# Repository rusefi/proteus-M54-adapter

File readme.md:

Proteus adapter for e46 non-M3 BMW

(E39 m54 should be the ms42/43 like the e46, E39 ~= E46)

https://github.com/rusefi/rusefi/wiki/BMW-e46

134 pin + Nissan board outline

https://raw.githubusercontent.com/wiki/rusefi/rusefi/OEM-Docs/Bmw/3_Series_e46/2002_bmw_325_ecu.png

https://docs.google.com/spreadsheets/d/16_VjNrk-DbMP_yDqGFelwavrGfiC9wFp73RgForjQzM

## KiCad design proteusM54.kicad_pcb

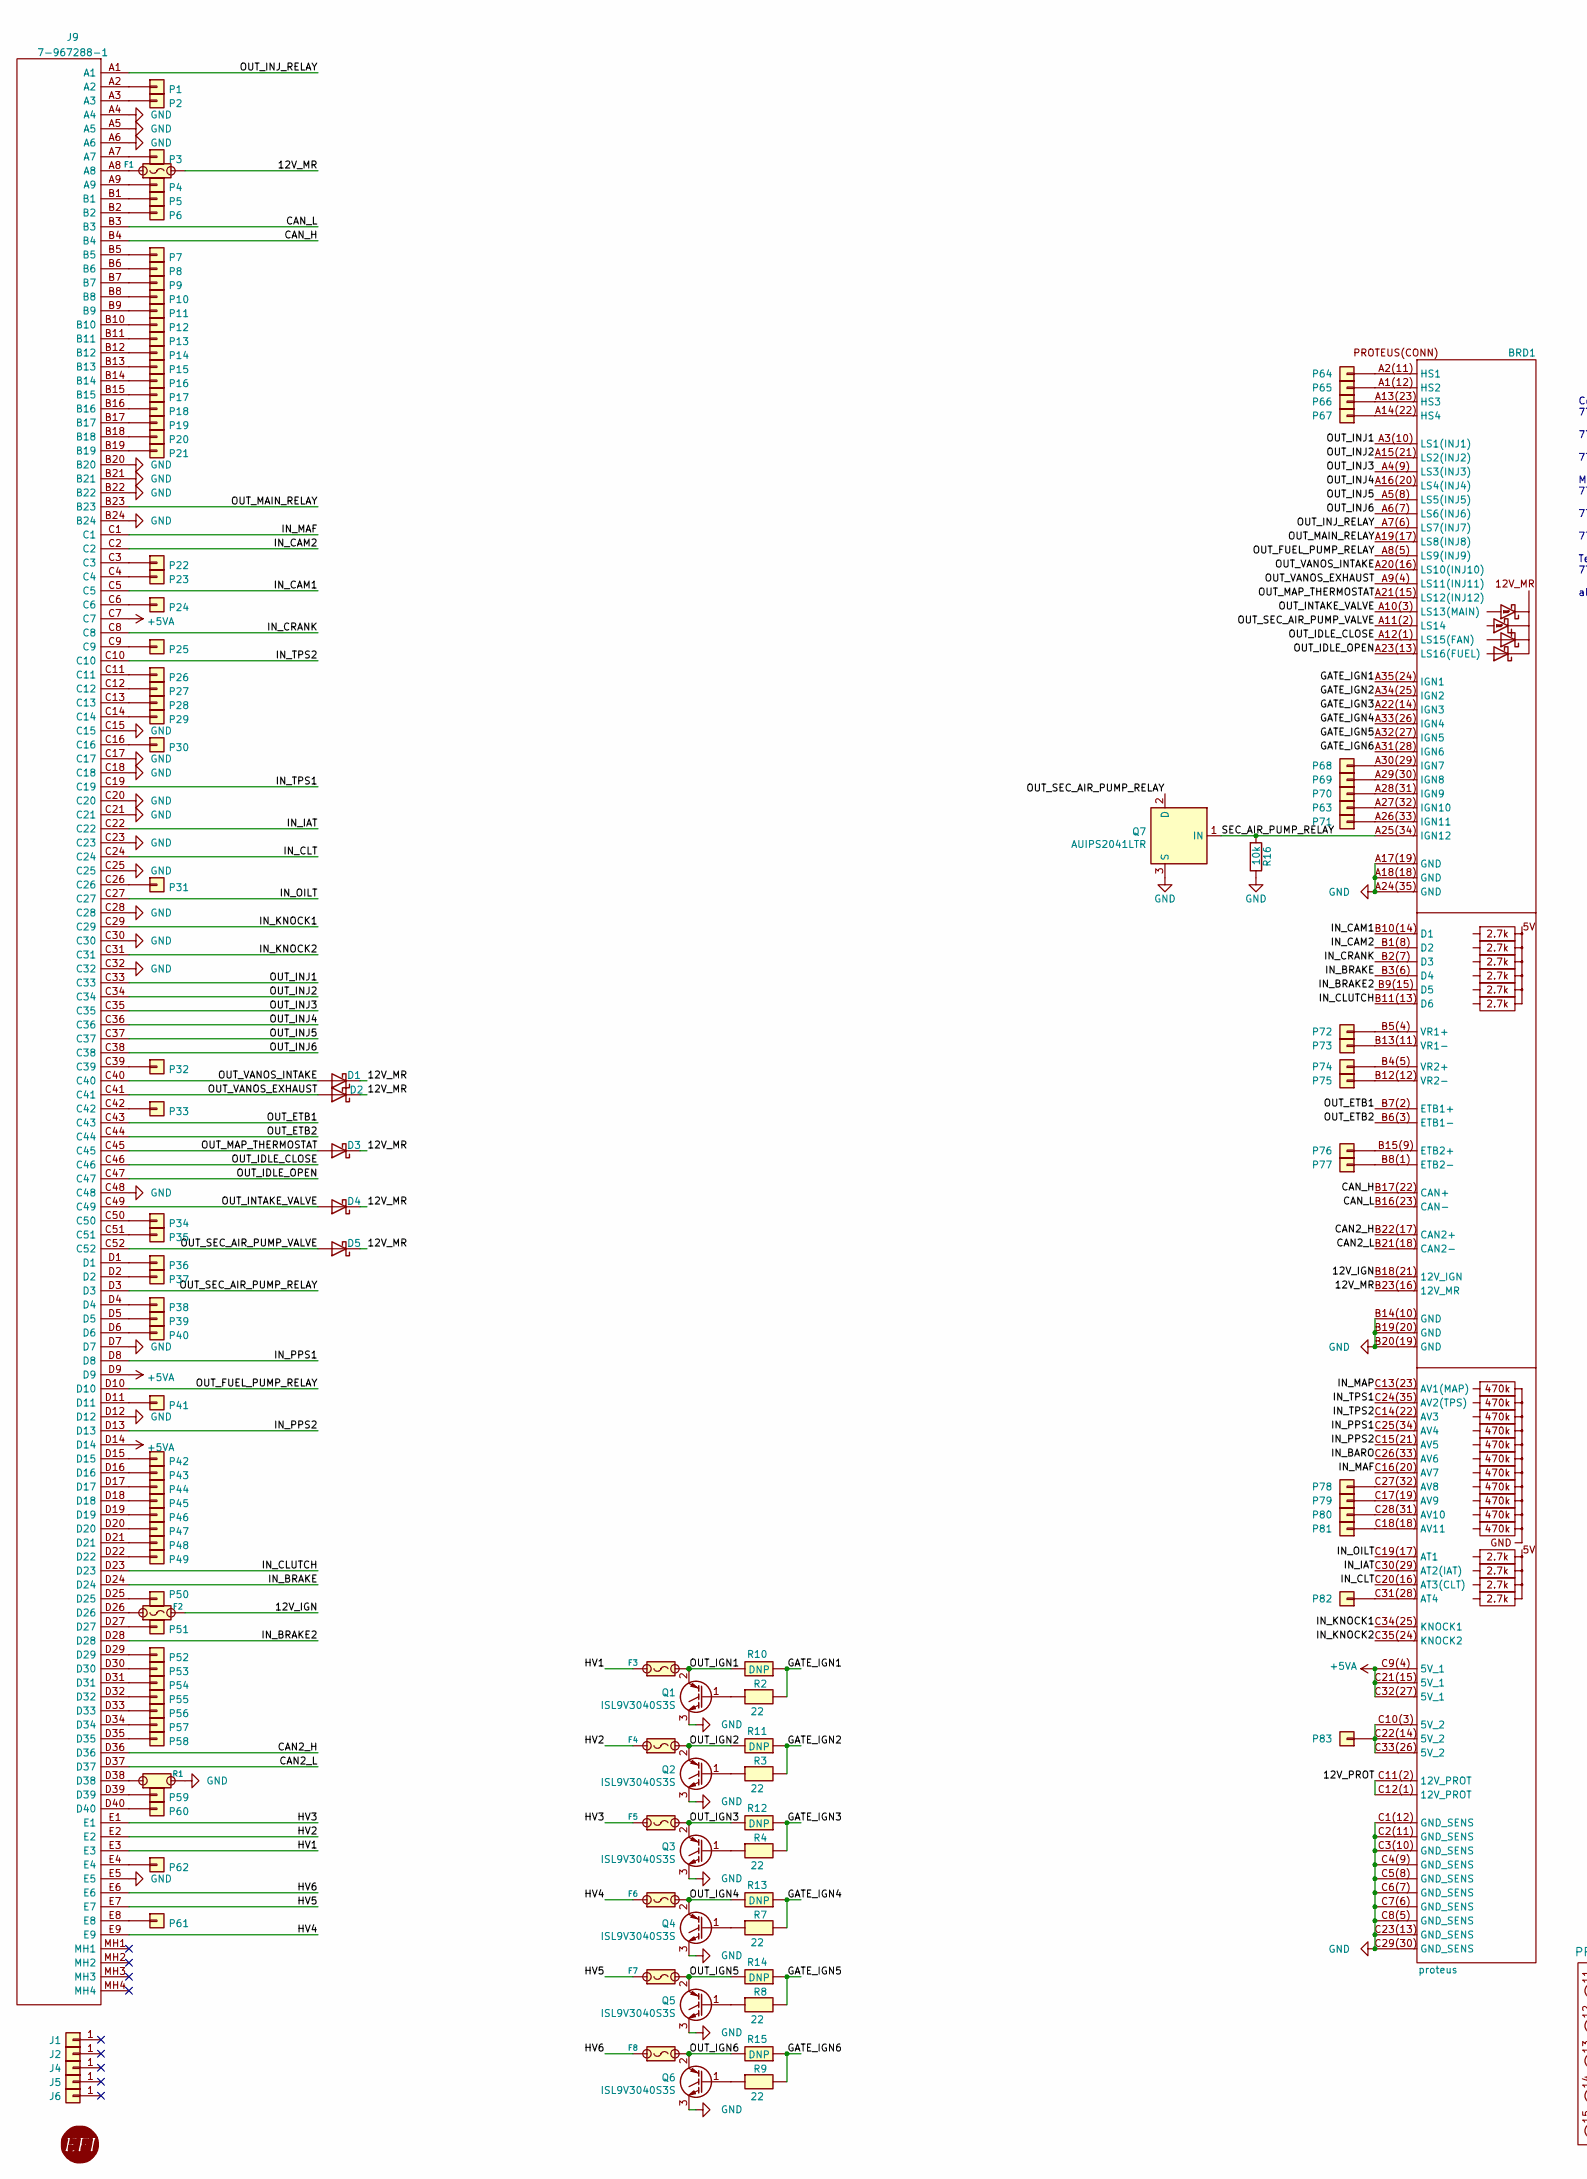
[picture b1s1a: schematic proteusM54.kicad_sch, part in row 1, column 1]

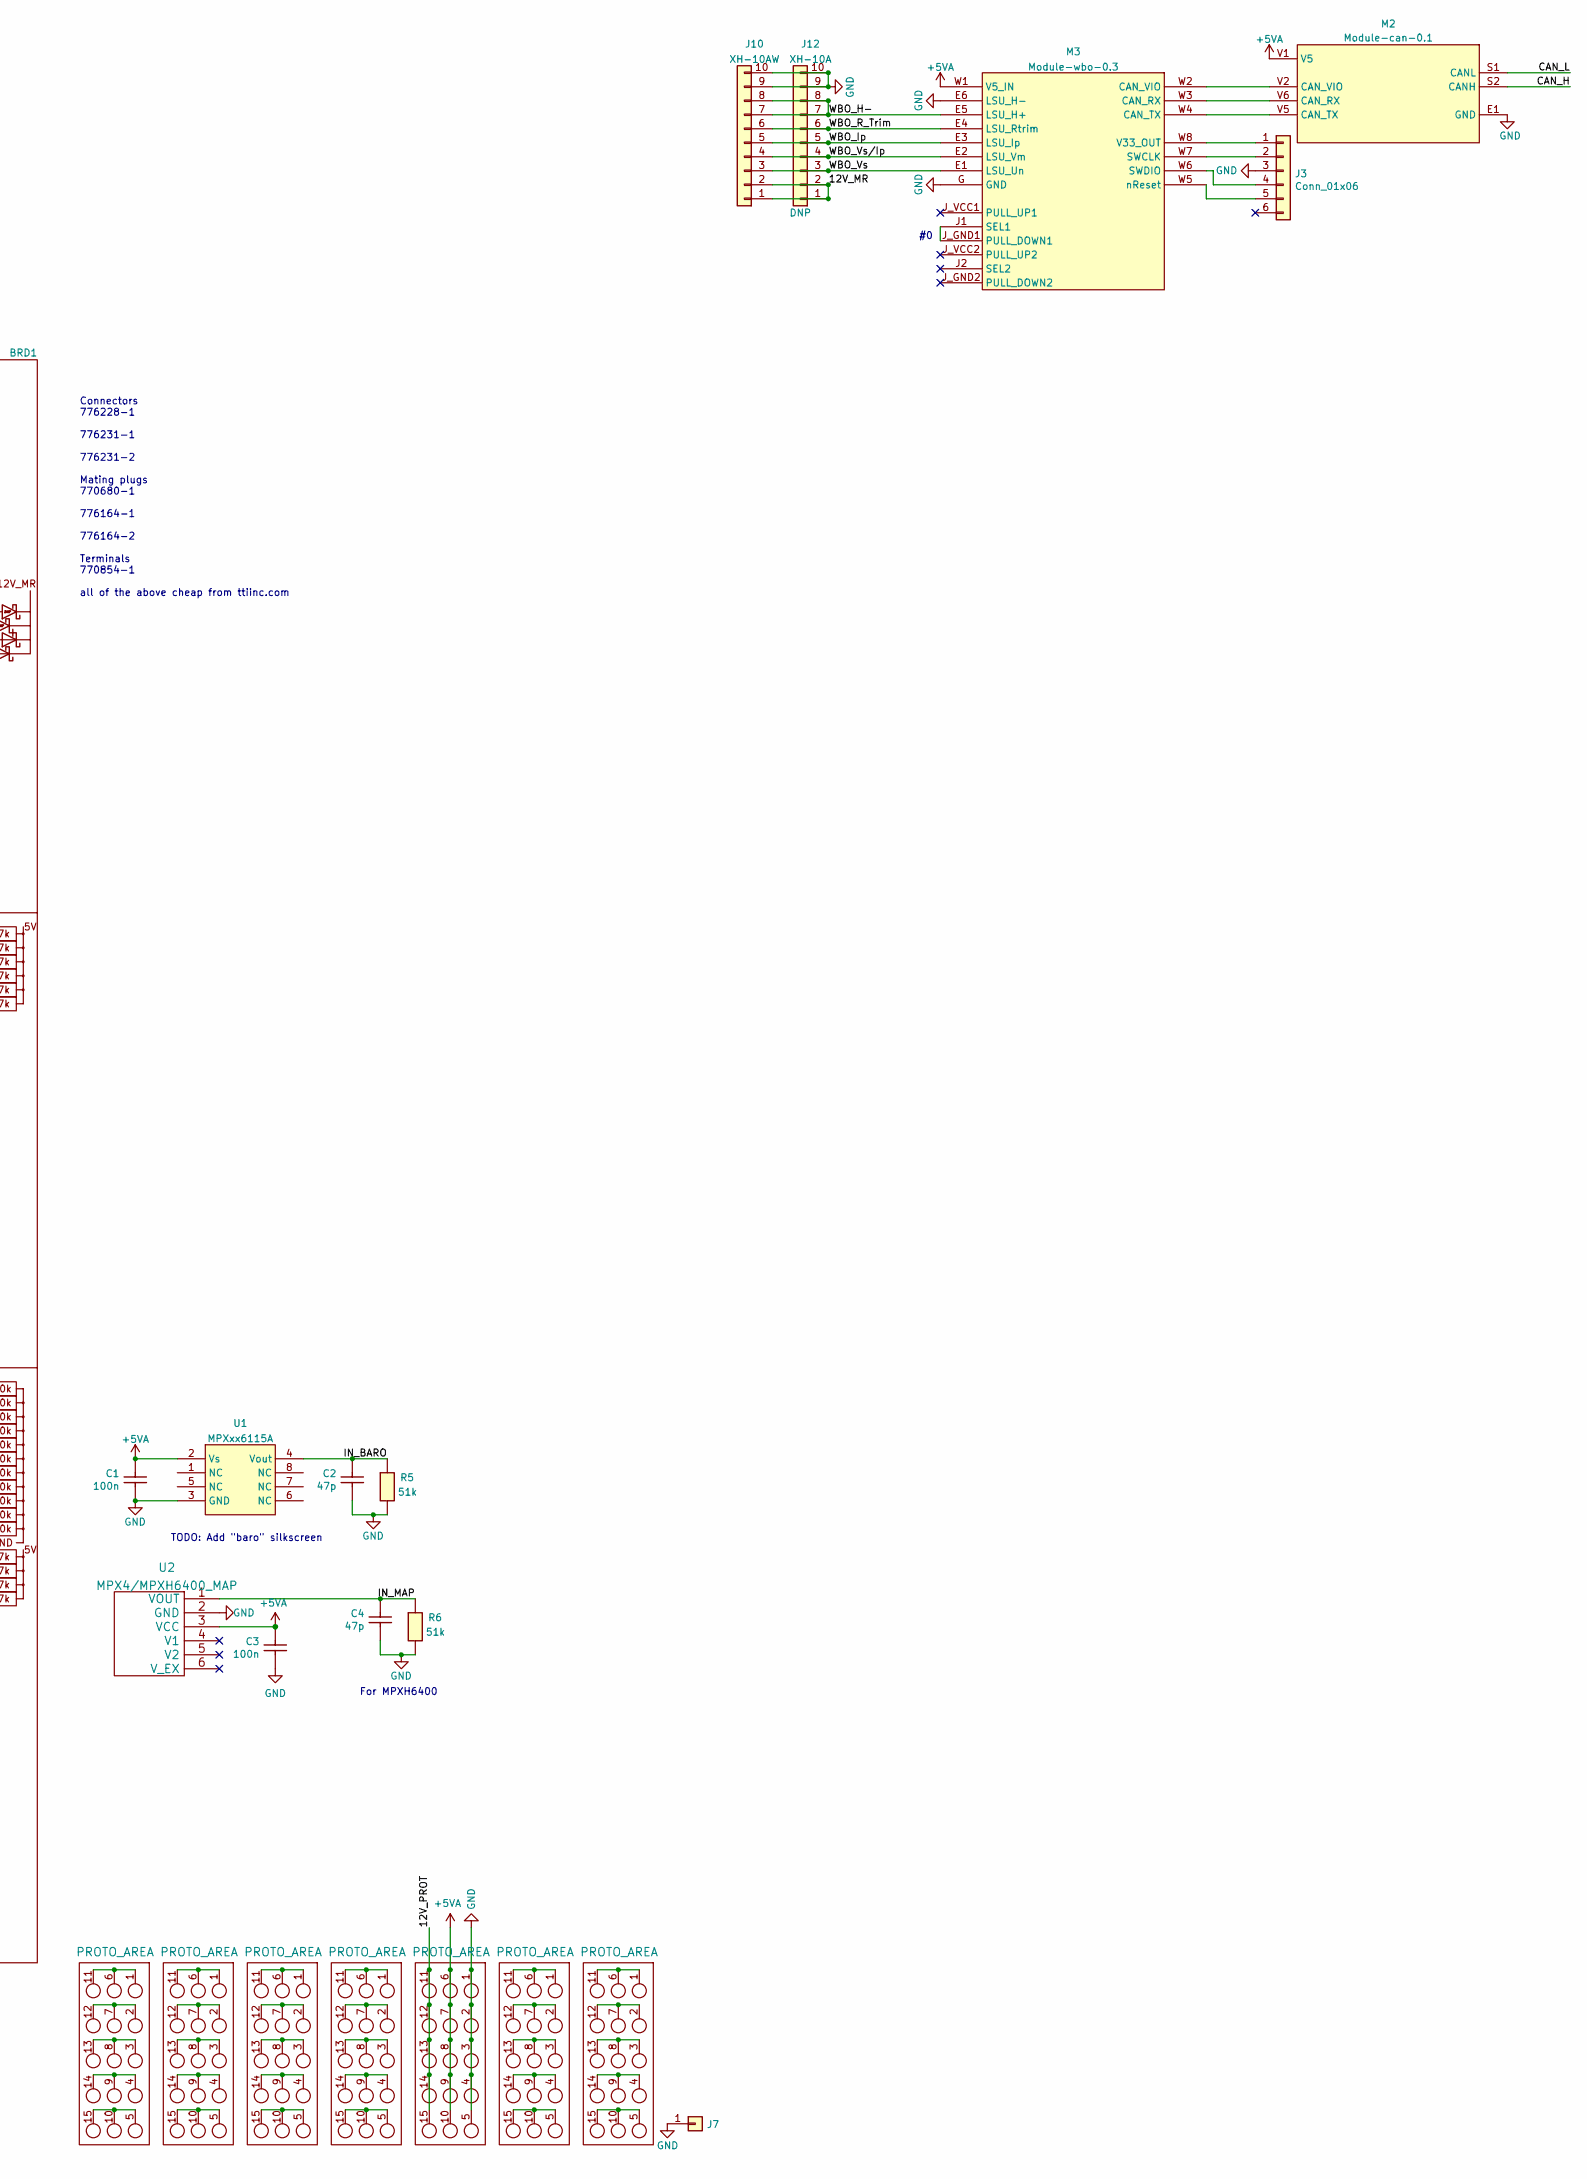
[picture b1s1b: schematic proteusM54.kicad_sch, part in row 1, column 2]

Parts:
BRD1: proteus
C1, C3: 100n; C0603; LCSC C14663
C2, C4: 47p; C0603; LCSC C1671
D1, D2, D3, D4, D5: D_Schottky; D_SMA; LCSC C8678
F1, F2: Fuse-Pad-Pad; PAD-1206-PAD; LCSC C182446
F3, F4, F5, F6, F7, F8: 10A; 36911600000; LCSC C354908
G1: RUSEFI_LOGO; rusefi_logo
G2, G3, G4, G5, G6, G7, G8: PROTO_AREA
J1, J2: Conn_01x01; MountingHole_3.5mm
J3: Conn_01x06; PinHeader_1x06_P2.54mm_Vertical
J4, J5: Conn_01x01; MountingHole_5.5mm
J6: Conn_01x01; MountingHole_4.5mm
J7: Conn_01x01; TestPoint_Pad_D4.0mm
J9: 7-967288-1; TE_7-967288-1; Mouser Part Number 571-7-967288-1
J10: XH-10AW; JST_XH_S10B-XH-A_1x10_P2.50mm_Horizontal; LCSC C14652
J12: XH-10A; JST_XH_B10B-XH-A_1x10_P2.50mm_Vertical; LCSC C8885
M2: Module-can-0.1; can
M3: Module-wbo-0.3; wbo
P1, P2, P3, P4, P5, P6, P7, P8, P9, P10, P11, P12, P13, P14, P15, P16, P17, P18, P19, P20, P21, P22, P23, P24, P25, P26, P27, P28, P29, P30, P31, P32, P33, P34, P35, P36, P37, P38, P39, P40, P41, P42, P43, P44, P45, P46, P47, P48, P49, P50, P51, P52, P53, P54, P55, P56, P57, P58, P59, P60, P61, P62, P63, P64, P65, P66, P67, P68, P69, P70, P71, P72, P73, P74, P75, P76, P77, P78, P79, P80, P81, P82, P83: Pad; PAD-TH
Q1, Q2, Q3, Q4, Q5, Q6: ISL9V3040S3S; TO-263-2; LCSC C898702
Q7: AUIPS2041LTR; SOT-223; LCSC C113610
R1: Jumper-Pad-Pad; PAD-0805-PAD; LCSC C17477
R2, R3, R4, R7, R8, R9: 22; R0603; LCSC C23345
R5, R6: 51k; R0603; LCSC C23196
R10, R11, R12, R13, R14, R15: DNP; R_2512_6332Metric
R16: 10k; R_0402_1005Metric; LCSC C60489
U1: MPXxx6115A; MPX_SOP_SSOP
U2: MPX4/MPXH6400_MAP; MPX-4_MAP

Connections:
+5VA: BRD1.C9(4) (5V_1), BRD1.C21(15) (5V_1), BRD1.C32(27) (5V_1), C1.2, C3.2, G6.6, G6.7, G6.8, G6.9, G6.10, J9.C7, J9.D9, J9.D14, M2.V1 (V5), M3.W1 (V5_IN), U1.2 (Vs), U2.3 (VCC)
/12V_IGN: BRD1.B18(21) (12V_IGN), F2.2
/12V_MR: BRD1.B23(16) (12V_MR), D1.1 (K), D2.1 (K), D3.1 (K), D4.1 (K), D5.1 (K), F1.2, J10.1, J10.2, J12.1, J12.2
/12V_PROT: BRD1.C11(2) (12V_PROT), BRD1.C12(1) (12V_PROT), G6.11, G6.12, G6.13, G6.14, G6.15
/CAN2_H: BRD1.B22(17) (CAN2+), J9.D36
/CAN2_L: BRD1.B21(18) (CAN2-), J9.D37
/CAN_H: BRD1.B17(22) (CAN+), J9.B4, M2.S2 (CANH)
/CAN_L: BRD1.B16(23) (CAN-), J9.B3, M2.S1 (CANL)
/GATE_IGN1: BRD1.A35(24) (IGN1), R2.2, R10.1
/GATE_IGN2: BRD1.A34(25) (IGN2), R3.2, R11.1
/GATE_IGN3: BRD1.A22(14) (IGN3), R4.2, R12.1
/GATE_IGN4: BRD1.A33(26) (IGN4), R7.2, R13.1
/GATE_IGN5: BRD1.A32(27) (IGN5), R8.2, R14.1
/GATE_IGN6: BRD1.A31(28) (IGN6), R9.2, R15.1
/HV1: F3.1, J9.E3
/HV2: F4.1, J9.E2
/HV3: F5.1, J9.E1
/HV4: F6.1, J9.E9
/HV5: F7.1, J9.E7
/HV6: F8.1, J9.E6
/IN_BARO: BRD1.C26(33) (AV6), C2.2, R5.1, U1.4 (Vout)
/IN_BRAKE: BRD1.B3(6) (D4), J9.D24
/IN_BRAKE2: BRD1.B9(15) (D5), J9.D28
/IN_CAM1: BRD1.B10(14) (D1), J9.C5
/IN_CAM2: BRD1.B1(8) (D2), J9.C2
/IN_CLT: BRD1.C20(16) (AT3(CLT)), J9.C24
/IN_CLUTCH: BRD1.B11(13) (D6), J9.D23
/IN_CRANK: BRD1.B2(7) (D3), J9.C8
/IN_IAT: BRD1.C30(29) (AT2(IAT)), J9.C22
/IN_KNOCK1: BRD1.C34(25) (KNOCK1), J9.C29
/IN_KNOCK2: BRD1.C35(24) (KNOCK2), J9.C31
/IN_MAF: BRD1.C16(20) (AV7), J9.C1
/IN_MAP: BRD1.C13(23) (AV1(MAP)), C4.2, R6.1, U2.1 (VOUT)
/IN_OILT: BRD1.C19(17) (AT1), J9.C27
/IN_PPS1: BRD1.C25(34) (AV4), J9.D8
/IN_PPS2: BRD1.C15(21) (AV5), J9.D13
/IN_TPS1: BRD1.C24(35) (AV2(TPS)), J9.C19
/IN_TPS2: BRD1.C14(22) (AV3), J9.C10
/OUT_ETB1: BRD1.B7(2) (ETB1+), J9.C43
/OUT_ETB2: BRD1.B6(3) (ETB1-), J9.C44
/OUT_FUEL_PUMP_RELAY: BRD1.A8(5) (LS9(INJ9)), J9.D10
/OUT_IDLE_CLOSE: BRD1.A12(1) (LS15(FAN)), J9.C46
/OUT_IDLE_OPEN: BRD1.A23(13) (LS16(FUEL)), J9.C47
/OUT_IGN1: F3.2, Q1.2 (C), R10.2
/OUT_IGN2: F4.2, Q2.2 (C), R11.2
/OUT_IGN3: F5.2, Q3.2 (C), R12.2
/OUT_IGN4: F6.2, Q4.2 (C), R13.2
/OUT_IGN5: F7.2, Q5.2 (C), R14.2
/OUT_IGN6: F8.2, Q6.2 (C), R15.2
/OUT_INJ1: BRD1.A3(10) (LS1(INJ1)), J9.C33
/OUT_INJ2: BRD1.A15(21) (LS2(INJ2)), J9.C34
/OUT_INJ3: BRD1.A4(9) (LS3(INJ3)), J9.C35
/OUT_INJ4: BRD1.A16(20) (LS4(INJ4)), J9.C36
/OUT_INJ5: BRD1.A5(8) (LS5(INJ5)), J9.C37
/OUT_INJ6: BRD1.A6(7) (LS6(INJ6)), J9.C38
/OUT_INJ_RELAY: BRD1.A7(6) (LS7(INJ7)), J9.A1
/OUT_INTAKE_VALVE: BRD1.A10(3) (LS13(MAIN)), D4.2 (A), J9.C49
/OUT_MAIN_RELAY: BRD1.A19(17) (LS8(INJ8)), J9.B23
/OUT_MAP_THERMOSTAT: BRD1.A21(15) (LS12(INJ12)), D3.2 (A), J9.C45
/OUT_SEC_AIR_PUMP_RELAY: J9.D3, Q7.2 (D)
/OUT_SEC_AIR_PUMP_VALVE: BRD1.A11(2) (LS14), D5.2 (A), J9.C52
/OUT_VANOS_EXHAUST: BRD1.A9(4) (LS11(INJ11)), D2.2 (A), J9.C41
/OUT_VANOS_INTAKE: BRD1.A20(16) (LS10(INJ10)), D1.2 (A), J9.C40
/SEC_AIR_PUMP_RELAY: BRD1.A25(34) (IGN12), Q7.1 (IN), R16.2
/WBO_H-: J10.7, J10.8, J12.7, J12.8, M3.E5 (LSU_H+)
/WBO_Ip: J10.5, J12.5, M3.E3 (LSU_Ip)
/WBO_R_Trim: J10.6, J12.6, M3.E4 (LSU_Rtrim)
/WBO_Vs: J10.3, J12.3, M3.E1 (LSU_Un)
/WBO_Vs/Ip: J10.4, J12.4, M3.E2 (LSU_Vm)
GND: BRD1.A17(19) (GND), BRD1.A18(18) (GND), BRD1.A24(35) (GND), BRD1.B14(10) (GND), BRD1.B19(20) (GND), BRD1.B20(19) (GND), BRD1.C1(12) (GND_SENS), BRD1.C2(11) (GND_SENS), BRD1.C3(10) (GND_SENS), BRD1.C4(9) (GND_SENS), BRD1.C5(8) (GND_SENS), BRD1.C6(7) (GND_SENS), BRD1.C7(6) (GND_SENS), BRD1.C8(5) (GND_SENS), BRD1.C23(13) (GND_SENS), BRD1.C29(30) (GND_SENS), C1.1, C2.1, C3.1, C4.1, G6.1, G6.2, G6.3, G6.4, G6.5, J3.3, J7.1, J9.A4, J9.A5, J9.A6, J9.B20, J9.B21, J9.B22, J9.B24, J9.C15, J9.C17, J9.C18, J9.C20, J9.C21, J9.C23, J9.C25, J9.C28, J9.C30, J9.C32, J9.C48, J9.D7, J9.D12, J9.E5, J10.9, J10.10, J12.9, J12.10, M2.E1 (GND), M3.E6 (LSU_H-), M3.G (GND), Q1.3 (E), Q2.3 (E), Q3.3 (E), Q4.3 (E), Q5.3 (E), Q6.3 (E), Q7.3 (S), R1.2, R5.2, R6.2, R16.1, U1.3 (GND), U2.2 (GND)
unnamed: BRD1.A1(12) (HS2), P65.1
unnamed: BRD1.A2(11) (HS1), P64.1
unnamed: BRD1.A13(23) (HS3), P66.1
unnamed: BRD1.A14(22) (HS4), P67.1
unnamed: BRD1.A26(33) (IGN11), P71.1
unnamed: BRD1.A28(31) (IGN9), P70.1
unnamed: BRD1.A29(30) (IGN8), P69.1
unnamed: BRD1.A30(29) (IGN7), P68.1
unnamed: BRD1.B4(5) (VR2+), P74.1
unnamed: BRD1.B5(4) (VR1+), P72.1
unnamed: BRD1.B8(1) (ETB2-), P77.1
unnamed: BRD1.B12(12) (VR2-), P75.1
unnamed: BRD1.B13(11) (VR1-), P73.1
unnamed: BRD1.B15(9) (ETB2+), P76.1
unnamed: BRD1.C17(19) (AV9), P79.1
unnamed: BRD1.C18(18) (AV11), P81.1
unnamed: BRD1.C10(3) (5V_2), BRD1.C22(14) (5V_2), BRD1.C33(26) (5V_2), P83.1
unnamed: BRD1.C27(32) (AV8), P78.1
unnamed: BRD1.C28(31) (AV10), P80.1
unnamed: BRD1.C31(28) (AT4), P82.1
unnamed: F1.1, J9.A8
unnamed: F2.1, J9.D26
unnamed: G2.1, G2.6, G2.11
unnamed: G2.5, G2.10, G2.15
unnamed: G2.2, G2.7, G2.12
unnamed: G2.3, G2.8, G2.13
unnamed: G2.4, G2.9, G2.14
unnamed: G3.1, G3.6, G3.11
unnamed: G3.5, G3.10, G3.15
unnamed: G3.2, G3.7, G3.12
unnamed: G3.3, G3.8, G3.13
unnamed: G3.4, G3.9, G3.14
unnamed: G4.1, G4.6, G4.11
unnamed: G4.5, G4.10, G4.15
unnamed: G4.2, G4.7, G4.12
unnamed: G4.3, G4.8, G4.13
unnamed: G4.4, G4.9, G4.14
unnamed: G5.1, G5.6, G5.11
unnamed: G5.5, G5.10, G5.15
unnamed: G5.2, G5.7, G5.12
unnamed: G5.3, G5.8, G5.13
unnamed: G5.4, G5.9, G5.14
unnamed: G7.1, G7.6, G7.11
unnamed: G7.5, G7.10, G7.15
unnamed: G7.2, G7.7, G7.12
unnamed: G7.3, G7.8, G7.13
unnamed: G7.4, G7.9, G7.14
unnamed: G8.1, G8.6, G8.11
unnamed: G8.5, G8.10, G8.15
unnamed: G8.2, G8.7, G8.12
unnamed: G8.3, G8.8, G8.13
unnamed: G8.4, G8.9, G8.14
unnamed: J3.1, M3.W8 (V33_OUT)
unnamed: J3.2, M3.W7 (SWCLK)
unnamed: J3.4, M3.W6 (SWDIO)
unnamed: J3.5, M3.W5 (nReset)
unnamed: J9.A2, P1.1
unnamed: J9.A3, P2.1
unnamed: J9.A7, P3.1
unnamed: J9.A9, P4.1
unnamed: J9.B1, P5.1
unnamed: J9.B2, P6.1
unnamed: J9.B5, P7.1
unnamed: J9.B6, P8.1
unnamed: J9.B7, P9.1
unnamed: J9.B8, P10.1
unnamed: J9.B9, P11.1
unnamed: J9.B10, P12.1
unnamed: J9.B11, P13.1
unnamed: J9.B12, P14.1
unnamed: J9.B13, P15.1
unnamed: J9.B14, P16.1
unnamed: J9.B15, P17.1
unnamed: J9.B16, P18.1
unnamed: J9.B17, P19.1
unnamed: J9.B18, P20.1
unnamed: J9.B19, P21.1
unnamed: J9.C3, P22.1
unnamed: J9.C4, P23.1
unnamed: J9.C6, P24.1
unnamed: J9.C9, P25.1
unnamed: J9.C11, P26.1
unnamed: J9.C12, P27.1
unnamed: J9.C13, P28.1
unnamed: J9.C14, P29.1
unnamed: J9.C16, P30.1
unnamed: J9.C26, P31.1
unnamed: J9.C39, P32.1
unnamed: J9.C42, P33.1
unnamed: J9.C50, P34.1
unnamed: J9.C51, P35.1
unnamed: J9.D1, P36.1
unnamed: J9.D2, P37.1
unnamed: J9.D4, P38.1
unnamed: J9.D5, P39.1
unnamed: J9.D6, P40.1
unnamed: J9.D11, P41.1
unnamed: J9.D15, P42.1
unnamed: J9.D16, P43.1
unnamed: J9.D17, P44.1
unnamed: J9.D18, P45.1
unnamed: J9.D19, P46.1
unnamed: J9.D20, P47.1
unnamed: J9.D21, P48.1
unnamed: J9.D22, P49.1
unnamed: J9.D25, P50.1
unnamed: J9.D27, P51.1
unnamed: J9.D29, P52.1
unnamed: J9.D30, P53.1
unnamed: J9.D31, P54.1
unnamed: J9.D32, P55.1
unnamed: J9.D33, P56.1
unnamed: J9.D34, P57.1
unnamed: J9.D35, P58.1
unnamed: J9.D38, R1.1
unnamed: J9.D39, P59.1
unnamed: J9.D40, P60.1
unnamed: J9.E4, P62.1
unnamed: J9.E8, P61.1
unnamed: M2.V2 (CAN_VIO), M3.W2 (CAN_VIO)
unnamed: M2.V5 (CAN_TX), M3.W4 (CAN_TX)
unnamed: M2.V6 (CAN_RX), M3.W3 (CAN_RX)
unnamed: M3.J1 (SEL1), M3.J_GND1 (PULL_DOWN1)
unnamed: BRD1.A27(32) (IGN10), P63.1
unnamed: Q1.1 (G), R2.1
unnamed: Q2.1 (G), R3.1
unnamed: Q3.1 (G), R4.1
unnamed: Q4.1 (G), R7.1
unnamed: Q5.1 (G), R8.1
unnamed: Q6.1 (G), R9.1

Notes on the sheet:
Connectors 776228-1 776231-1 776231-2 Mating plugs 770680-1 776164-1 776164-2 Terminals 770854-1 all of the above cheap from ttiinc.com
For MPXH6400
TODO: Add "baro" silkscreen

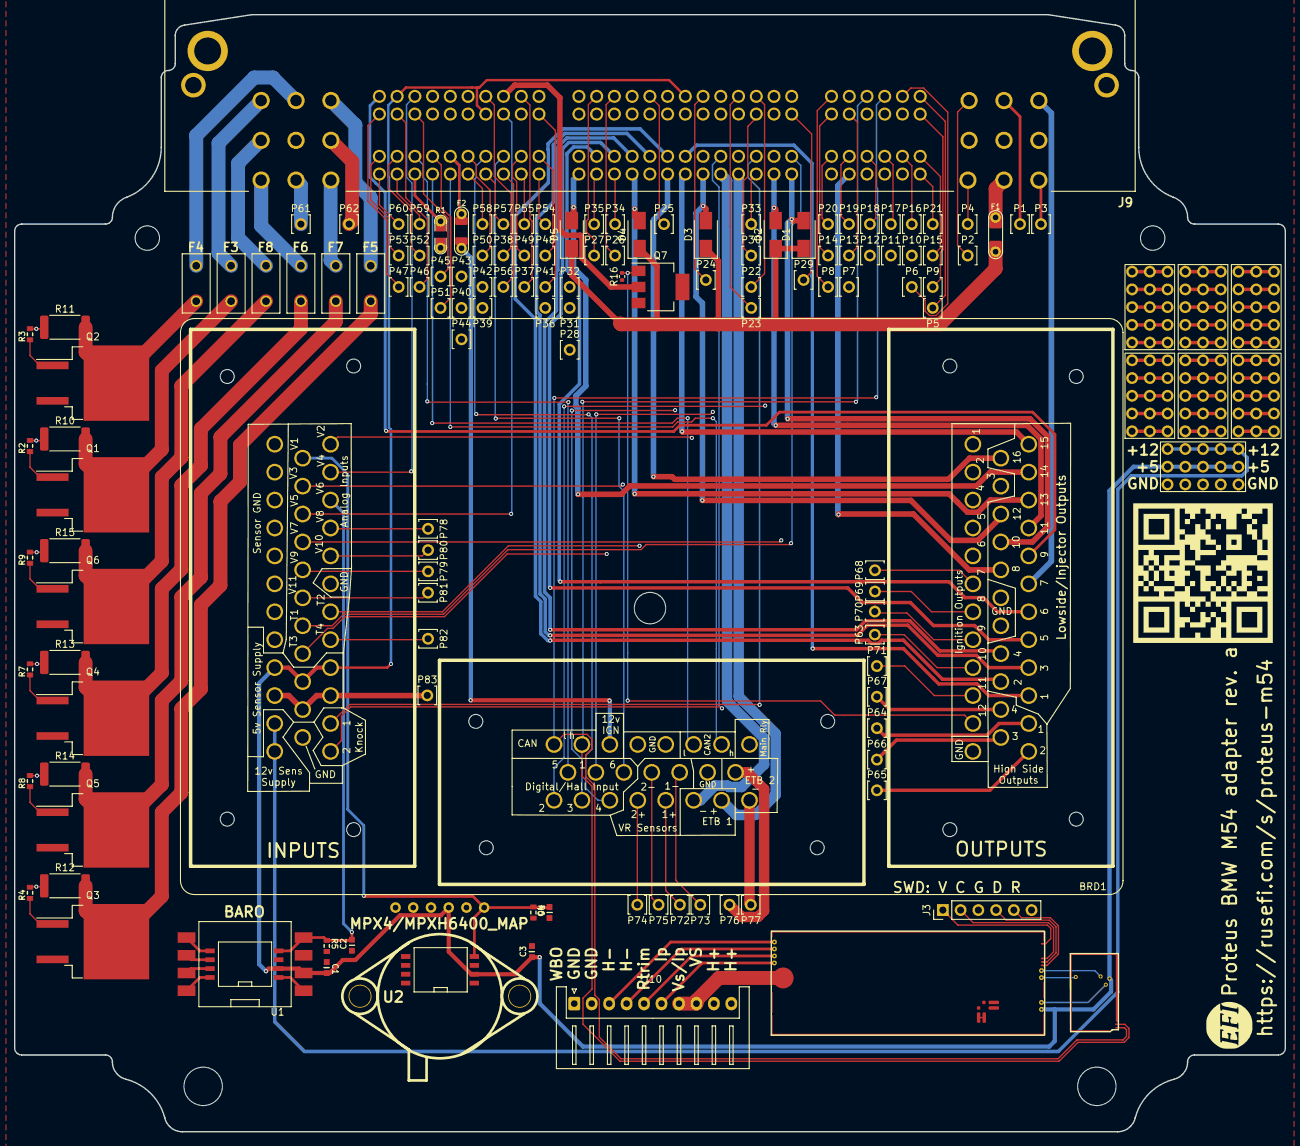
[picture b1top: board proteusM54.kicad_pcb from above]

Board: 4 copper layers, 182.0 x 160.0 mm, 145 parts (1 on the bottom side), 200 nets.

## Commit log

2021-10-05 Pinout
2021-11-10 Upd sch, pcb
2021-11-13 Upd pcb
2021-11-13 Fab preview
